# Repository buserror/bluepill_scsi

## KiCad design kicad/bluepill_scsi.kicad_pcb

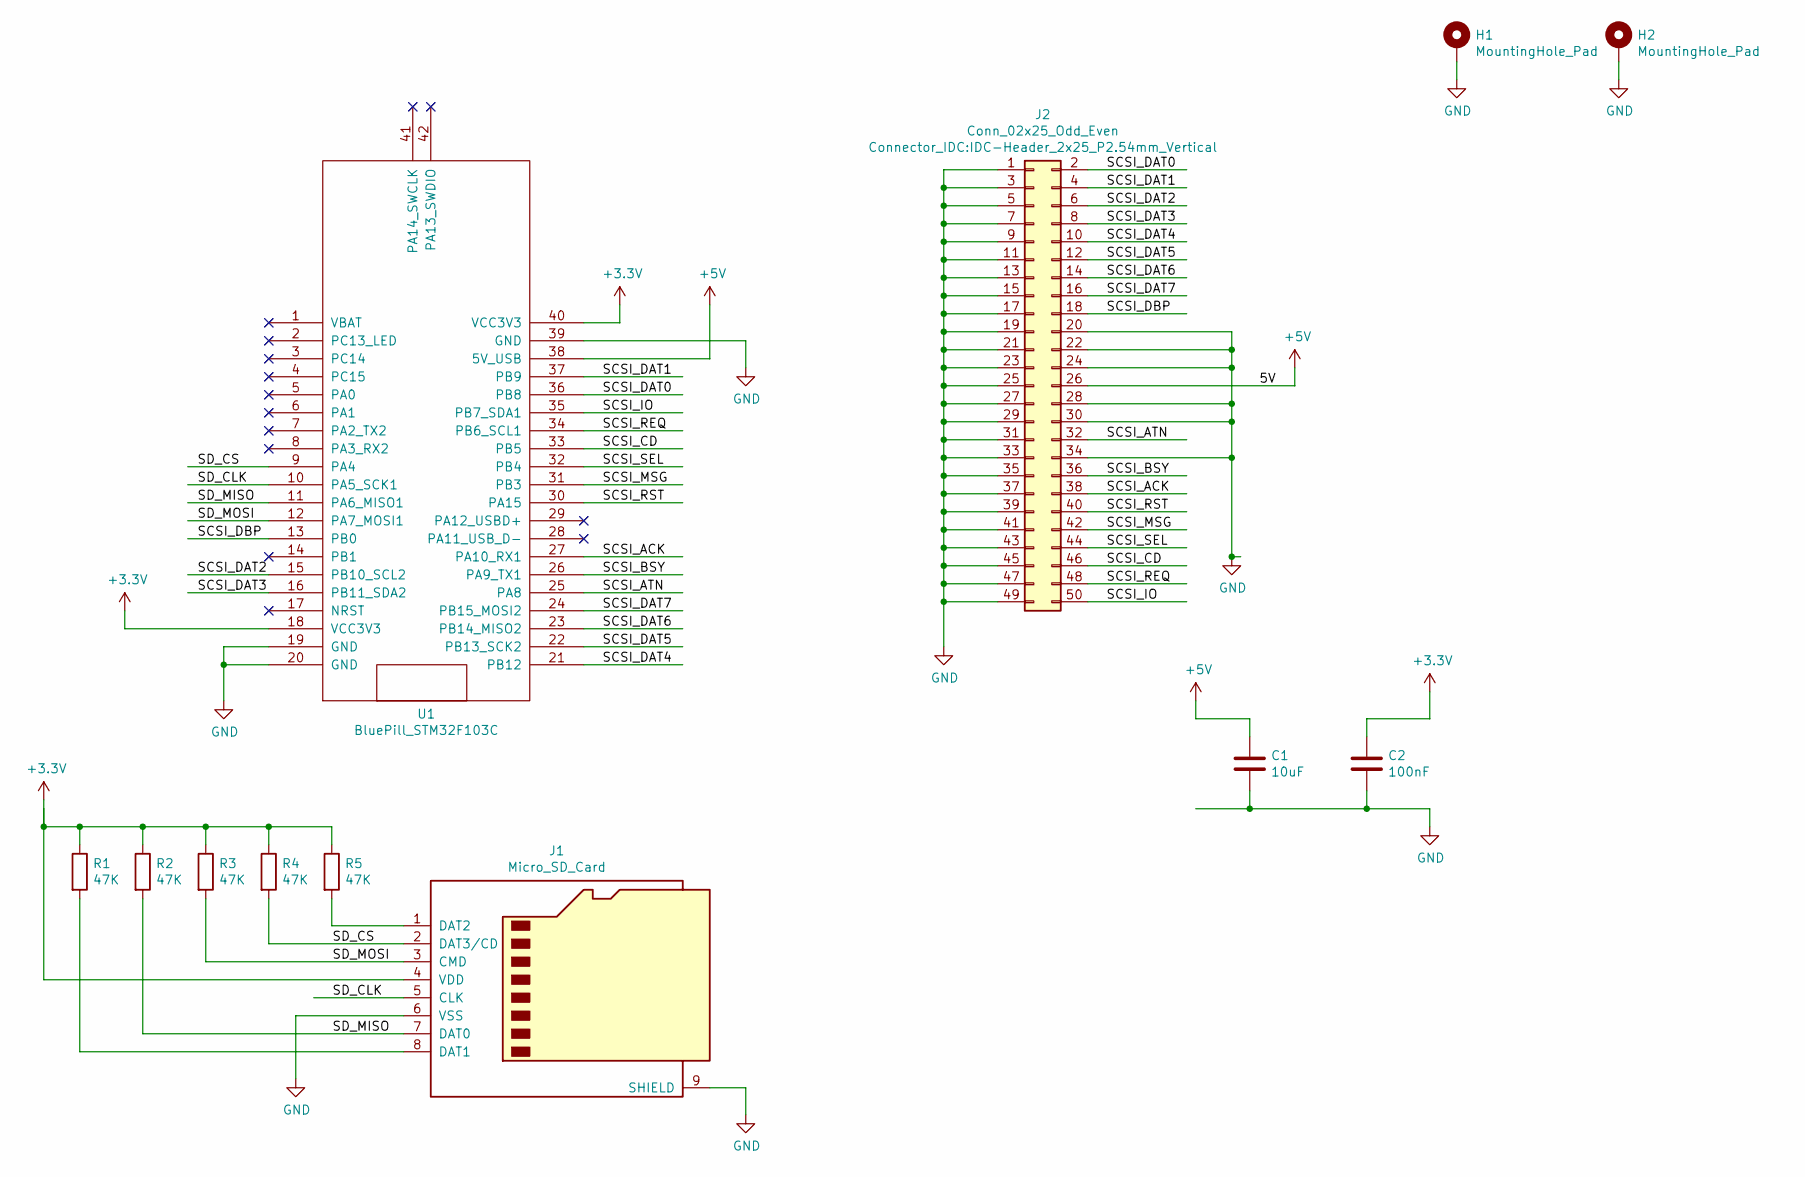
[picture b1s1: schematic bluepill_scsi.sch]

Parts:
C1: 10uF; C_0805_2012Metric
C2: 100nF; C_0603_1608Metric
H1, H2: MountingHole_Pad; MountingHole_2.7mm_M2.5
J1: Micro_SD_Card; microSD_HC_Molex_104031-0811
J2: Conn_02x25_Odd_Even; IDC-Header_2x25_P2.54mm_Vertical
R1, R2, R3, R4, R5: 47K; R_0603_1608Metric_Pad1.05x0.95mm_HandSolder
U1: BluePill_STM32F103C

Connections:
+3V3: C2.1, J1.4 (VDD), R1.1, R2.1, R3.1, R4.1, R5.1, U1.18 (VCC3V3), U1.40 (VCC3V3)
+5V: C1.1, J2.26, U1.38 (5V_USB)
/SCSI_ACK: J2.38, U1.27 (PA10_RX1)
/SCSI_ATN: J2.32, U1.25 (PA8)
/SCSI_BSY: J2.36, U1.26 (PA9_TX1)
/SCSI_CD: J2.46, U1.33 (PB5)
/SCSI_DAT0: J2.2, U1.36 (PB8)
/SCSI_DAT1: J2.4, U1.37 (PB9)
/SCSI_DAT2: J2.6, U1.15 (PB10_SCL2)
/SCSI_DAT3: J2.8, U1.16 (PB11_SDA2)
/SCSI_DAT4: J2.10, U1.21 (PB12)
/SCSI_DAT5: J2.12, U1.22 (PB13_SCK2)
/SCSI_DAT6: J2.14, U1.23 (PB14_MISO2)
/SCSI_DAT7: J2.16, U1.24 (PB15_MOSI2)
/SCSI_DBP: J2.18, U1.13 (PB0)
/SCSI_IO: J2.50, U1.35 (PB7_SDA1)
/SCSI_MSG: J2.42, U1.31 (PB3)
/SCSI_REQ: J2.48, U1.34 (PB6_SCL1)
/SCSI_RST: J2.40, U1.30 (PA15)
/SCSI_SEL: J2.44, U1.32 (PB4)
/SD_CLK: J1.5 (CLK), U1.10 (PA5_SCK1)
/SD_CS: J1.2 (DAT3/CD), R4.2, U1.9 (PA4)
/SD_MISO: J1.7 (DAT0), R2.2, U1.11 (PA6_MISO1)
/SD_MOSI: J1.3 (CMD), R3.2, U1.12 (PA7_MOSI1)
GND: C1.2, C2.2, H1.1, H2.1, J1.6 (VSS), J1.9 (SHIELD), J2.1, J2.3, J2.5, J2.7, J2.9, J2.11, J2.13, J2.15, J2.17, J2.19, J2.20, J2.21, J2.22, J2.23, J2.24, J2.25, J2.27, J2.28, J2.29, J2.30, J2.31, J2.33, J2.34, J2.35, J2.37, J2.39, J2.41, J2.43, J2.45, J2.47, J2.49, U1.19 (GND), U1.20 (GND), U1.39 (GND)
unnamed: J1.1 (DAT2), R5.2
unnamed: J1.8 (DAT1), R1.2

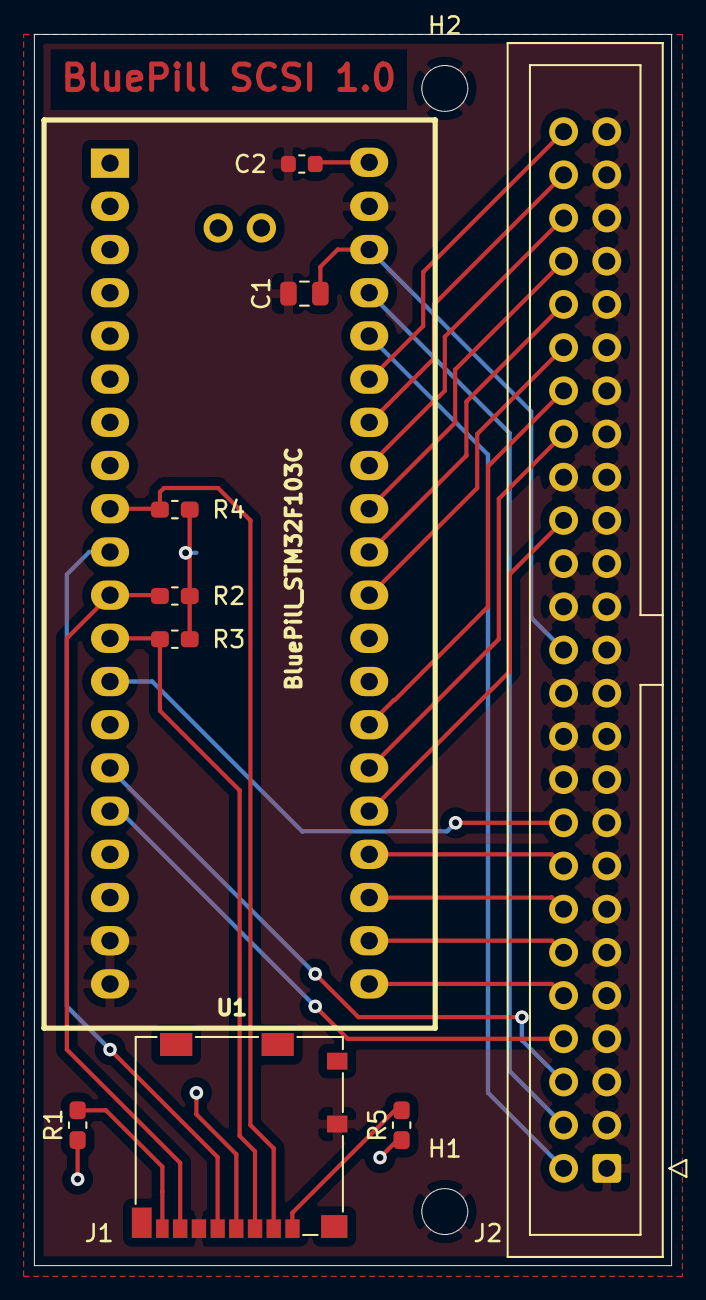
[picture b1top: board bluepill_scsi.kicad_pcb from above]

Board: 2 copper layers, 37.5 x 72.4 mm, 12 parts (0 on the bottom side), 27 nets.

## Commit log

2020-07-09 Initial commit
    Kicad schematic/board is the same as the old I ordered on OSHPARK.
    Source doesn't compile -- well it does but the SPI declaration is wrong.
    I've translated quickly SOME comments, but nowhere near as much as there
    is
